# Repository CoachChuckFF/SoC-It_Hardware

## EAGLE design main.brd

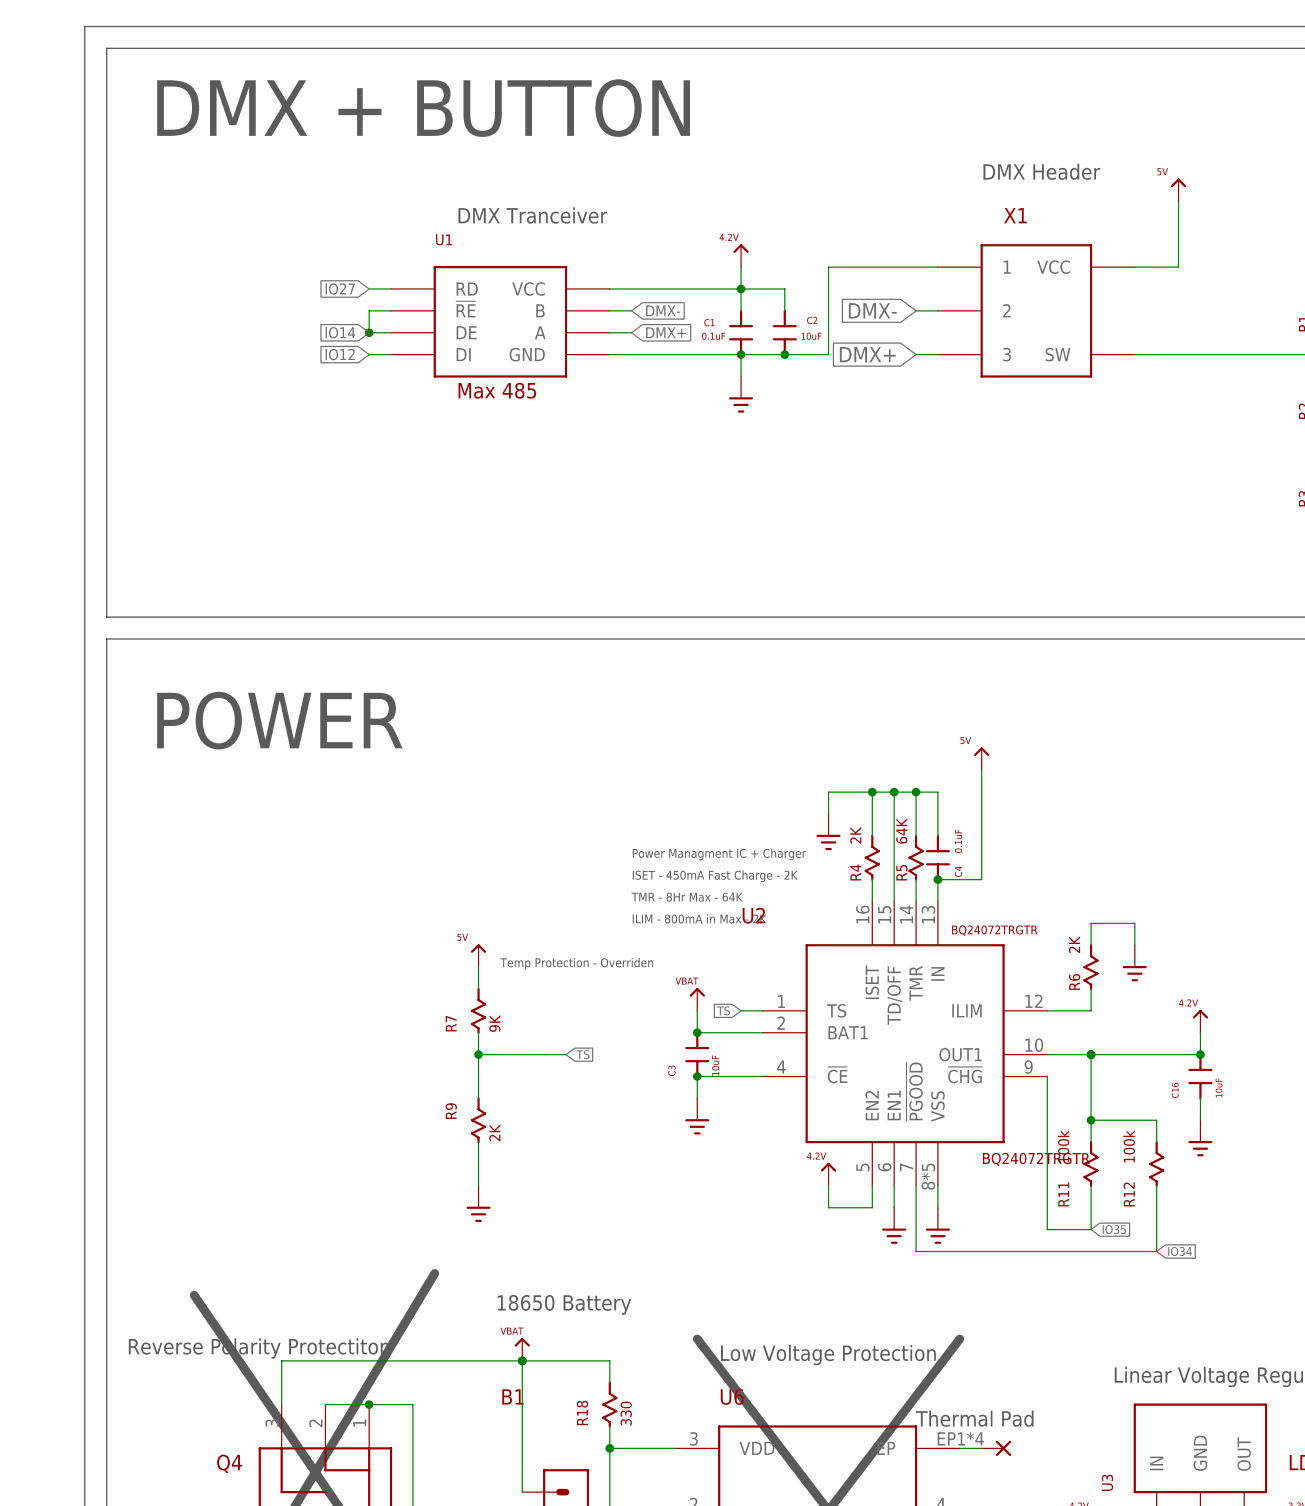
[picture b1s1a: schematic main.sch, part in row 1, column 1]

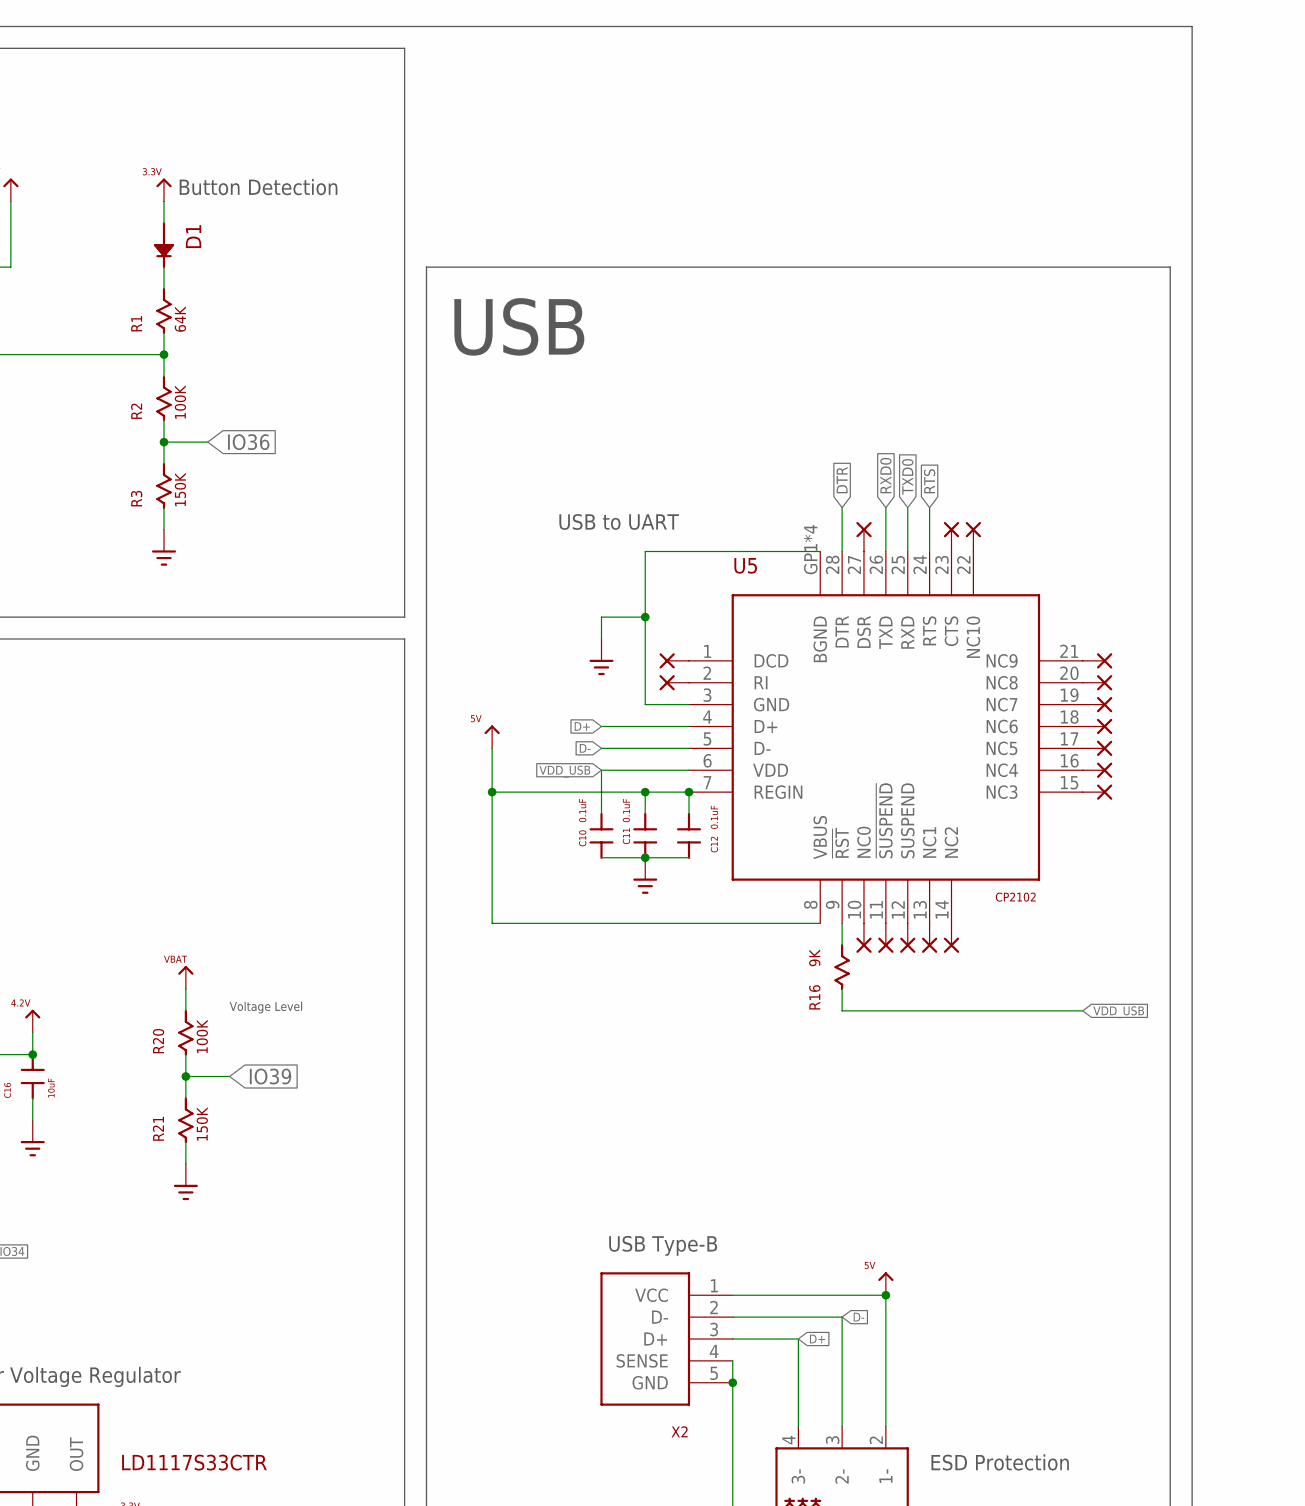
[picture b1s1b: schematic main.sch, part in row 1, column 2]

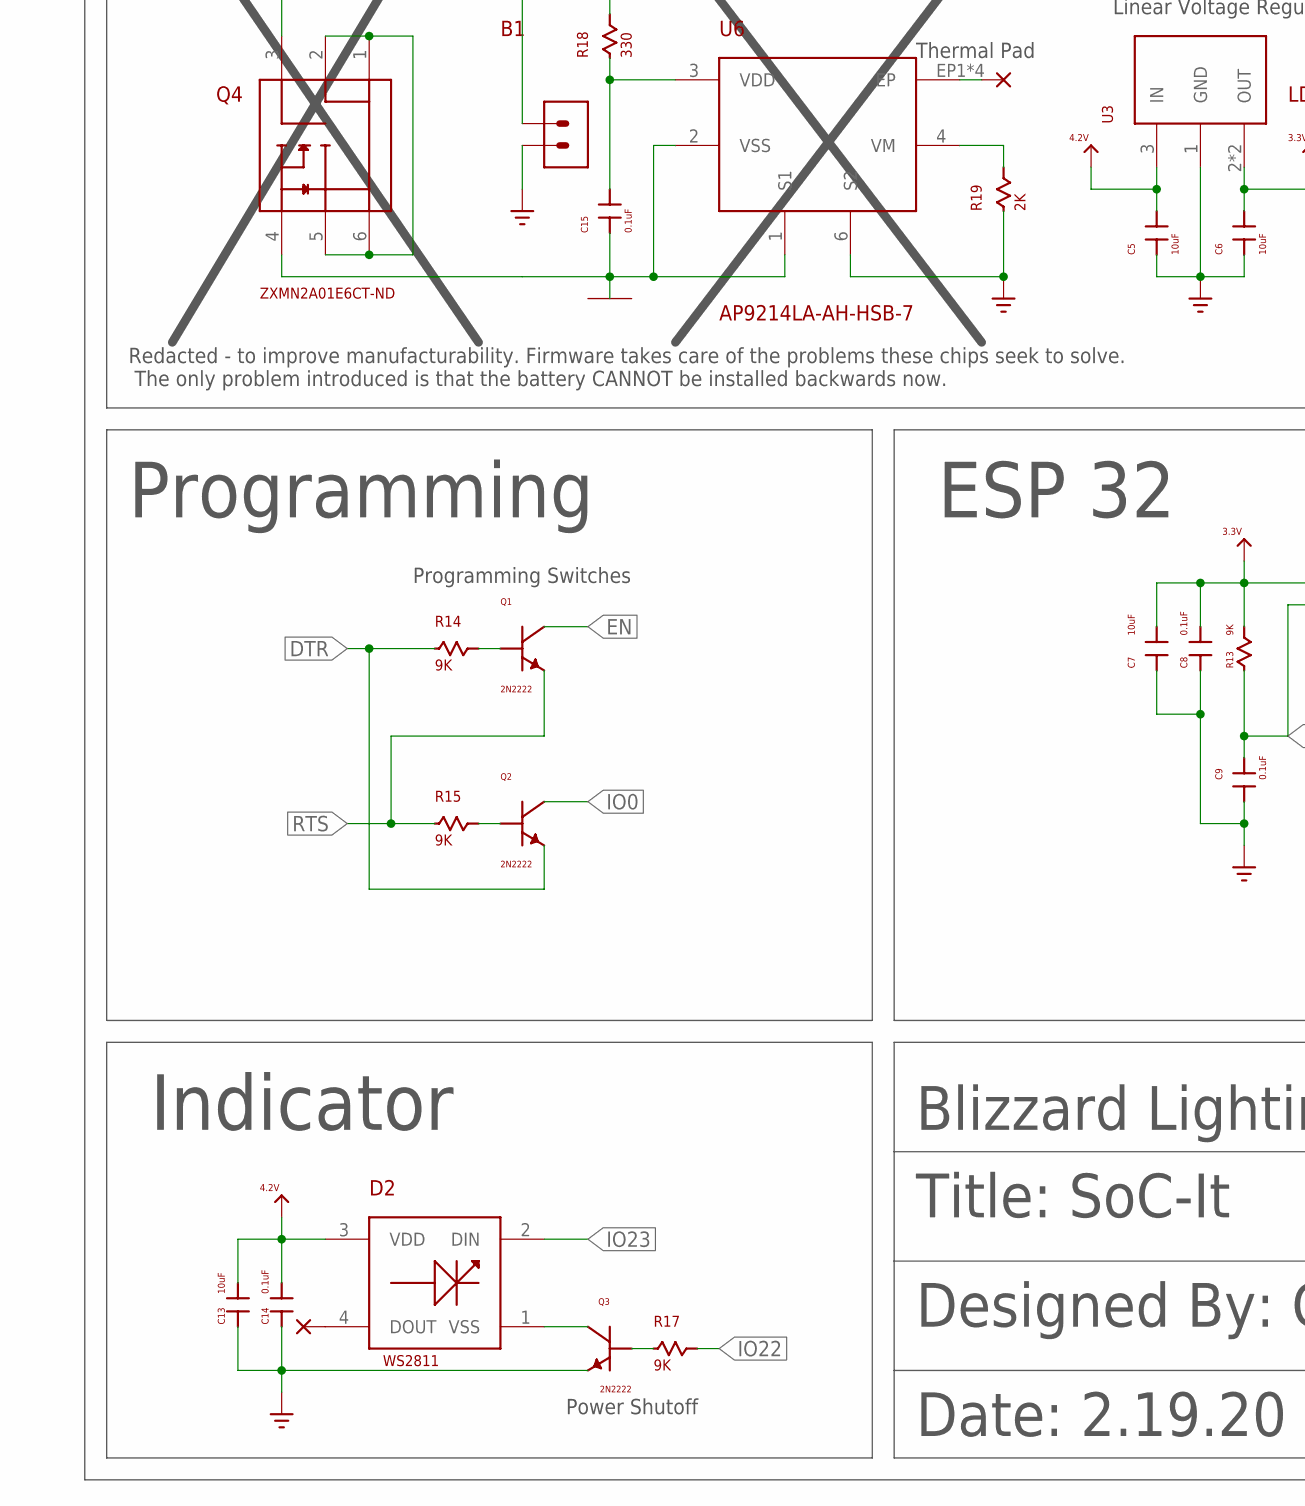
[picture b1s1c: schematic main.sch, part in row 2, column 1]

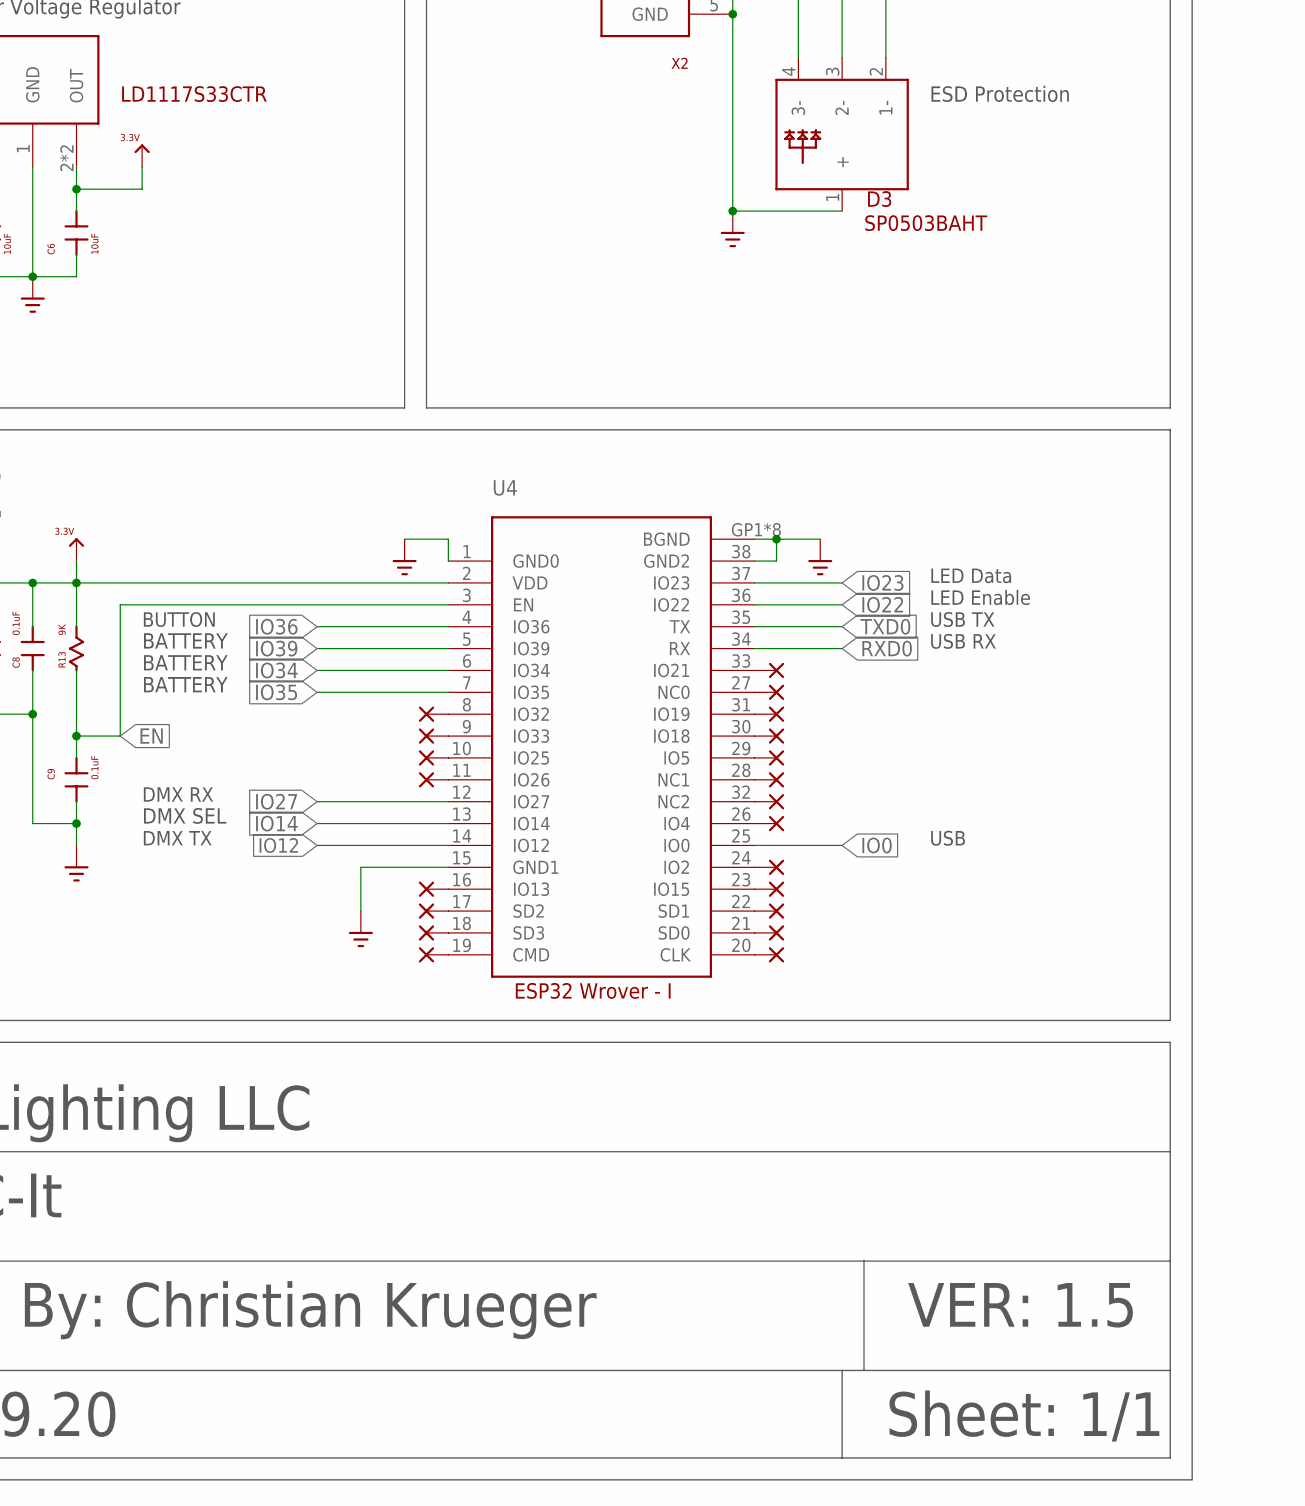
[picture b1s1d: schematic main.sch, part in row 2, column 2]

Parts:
B1: 18650_BATTERY_DEV; 18650_BATTERY_PKG
C1, C4, C8, C9, C10, C11, C12, C14, C15: 0.1uF; CAPC1508X55
C2, C3, C5, C6, C7, C13, C16: 10uF; CAPC1508X55
D1: 0603_DIODE_DEV; 0603_DIODE
D2: 5050_DEV; 5050_PKG
D3: USB_ESD_DEVSOT143; SOT192P237X122-4
Q1, Q2, Q3: 2N2222; SOT95P242X120-3
Q4: N_MOSFET_DEVSOT23-6L_PKG; SOT95P280X125-6
R1, R5: 64K; RESC1608X55
R2, R20: 100K; RESC1608X55
R3, R21: 150K; RESC1608X55
R4, R6, R9, R19: 2K; RESC1608X55
R7, R13, R14, R15, R16, R17: 9K; RESC1608X55
R11, R12: 100k; RESC1608X55
R18: 330; RESC1608X55
U1: MAX_485_DEV3D; SOIC127P600X175-8
U2: BQ24072TRGTR_DEVBQ24072TRGTR; QFN50P300X300X100-17T168
U3: LD1117S33CTR_DEVLD1117S33CTR; SOT230P700X180-4
U4: ESP_32_WROVER_I_PKG; ESP32_WROVER_I_PKG
U5: USB_TO_UART_DEV; QFN50P500X500X100-28
U6: AP9214L_DEV; U-DFN2535-6_PKG
X1: XLR_FEMALE_PLUG_DEV; XLR_FEMALE_PLUG_PKG
X2: USB_ALI_DEV; CHEAP_USB

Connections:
3.3V: C6.2, C7.2, C8.2, D1.A+, R13.2, U3.2 (OUT), U3.4 (OUT), U4.2 (VDD)
4.2V: C1.1, C2.1, C5.2, C13.2, C14.2, C16.2, D2.3 (VDD), R11.2, R12.2, U1.8 (VCC), U2.5 (EN2), U2.10 (OUT1), U3.3 (IN)
5V: C4.1, C11.2, C12.2, D3.2 (1-), R7.2, U2.13 (IN), U5.7 (REGIN), U5.8 (VBUS), X1.VCC, X2.1 (VCC)
BATTERY_GROUND: Q4.1 (D1), Q4.2 (D2), Q4.5 (D3), Q4.6 (D4)
D+: D3.4 (3-), U5.4 (D+), X2.3 (D+)
D-: D3.3 (2-), U5.5 (D-), X2.2 (D-)
DMX+: U1.6 (A), X1.3
DMX-: U1.7 (B), X1.2
DTR: Q2.2 (E), R14.1, U5.28 (DTR)
EN: C9.2, Q1.3 (C), R13.1, U4.3 (EN)
GND: B1.-, C1.2, C2.2, C3.1, C4.2, C5.1, C6.1, C7.1, C8.1, C9.1, C10.1, C11.1, C12.1, C13.1, C14.1, C16.1, D3.1 (+), Q3.2 (E), R3.1, R4.2, R5.2, R6.2, R9.1, R19.1, R21.1, U1.5 (GND), U2.4 (!CE), U2.6 (EN1), U2.8 (VSS), U2.15 (TD/OFF), U2.GP1 (VSS), U2.GP2 (VSS), U2.GP3 (VSS), U2.GP4 (VSS), U3.1 (GND), U4.1 (GND0), U4.15 (GND1), U4.38 (GND2), U4.GP1 (BGND), U4.GP2 (BGND), U4.GP3 (BGND), U4.GP4 (BGND), U4.GP5 (BGND), U4.GP6 (BGND), U4.GP8 (BGND), U4.GP9 (BGND), U5.3 (GND), U5.GP1 (BGND), U5.GP2 (BGND), U5.GP3 (BGND), U5.GP4 (BGND), U6.6 (S2), X1.1, X2.4 (SENSE), X2.5 (GND)
IO0: Q2.3 (C), U4.25 (IO0)
IO12: U1.4 (DI), U4.14 (IO12)
IO14: U1.2 (!RE), U1.3 (DE), U4.13 (IO14)
IO22: R17.2, U4.36 (IO22)
IO23: D2.2 (DIN), U4.37 (IO23)
IO27: U1.1 (RD), U4.12 (IO27)
IO34: R12.1, U2.7 (!PGOOD), U4.6 (IO34)
IO35: R11.1, U2.9 (!CHG), U4.7 (IO35)
IO36: R2.1, R3.2, U4.4 (IO36)
IO39: R20.1, R21.2, U4.5 (IO39)
unnamed: D2.1 (VSS), Q3.3 (C)
unnamed: Q1.1 (B), R14.2
unnamed: Q2.1 (B), R15.2
unnamed: Q3.1 (B), R17.1
unnamed: R16.2, U5.9 (!RST)
unnamed: D1.C-, R1.2
unnamed: R1.1, R2.2, X1.SW
unnamed: R19.2, U6.4 (VM)
unnamed: C15.2, R18.1, U6.3 (VDD)
unnamed: R6.1, U2.12 (ILIM)
unnamed: R5.1, U2.14 (TMR)
unnamed: R4.1, U2.16 (ISET)
PROTECTION_GROUND: C15.1, Q4.4 (S), U6.1 (S1), U6.2 (VSS)
PROTECTION_THERMAL_PAD: U6.EP1 (EP), U6.EP2 (EP), U6.EP3 (EP), U6.EP4 (EP)
RTS: Q1.2 (E), R15.1, U5.24 (RTS)
RXD0: U4.34 (RX), U5.26 (TXD)
TS: R7.1, R9.2, U2.1 (TS)
TXD0: U4.35 (TX), U5.25 (RXD)
VBAT: B1.+, C3.2, Q4.3 (G), R18.2, R20.2, U2.2 (BAT1)
VDD_USB: C10.2, R16.1, U5.6 (VDD)

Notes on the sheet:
USB
POWER
DMX RX
DMX TX
USB TX
USB RX
LED Data
DMX + BUTTON
ESP 32
Title: SoC-It
Designed By: Christian Krueger
Blizzard Lighting LLC
Date: 2.19.20
Sheet: 1/1
VER: 1.5
BUTTON
Programming Switches
USB Type-B
Linear Voltage Regulator
Max 485
DMX Header
DMX SEL
Programming
Indicator
BATTERY
LED Enable
CP2102
Button Detection
WS2811
ESD Protection
DMX Tranceiver
USB to UART
Power Shutoff
Thermal Pad
Low Voltage Protection
18650 Battery
BQ24072TRGTR
ISET - 450mA Fast Charge - 2K
TMR - 8Hr Max - 64K
ILIM - 800mA in Max - 2K

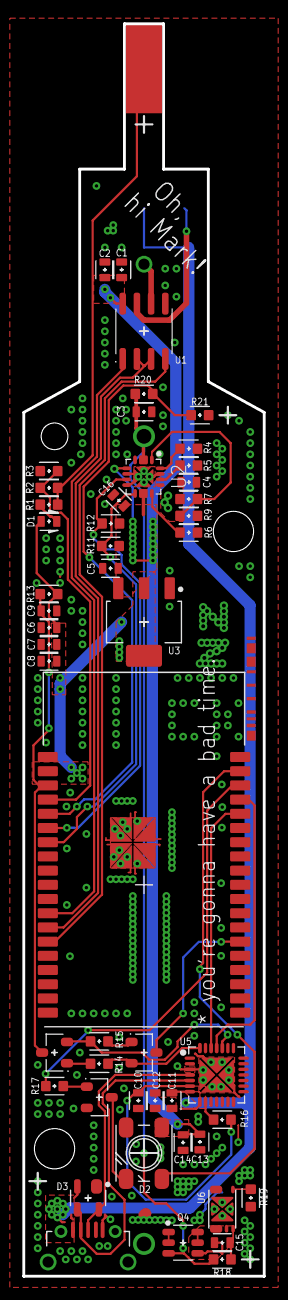
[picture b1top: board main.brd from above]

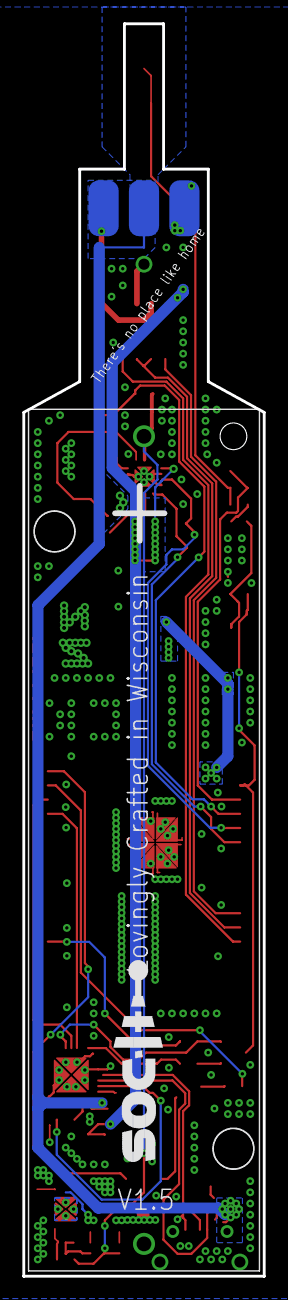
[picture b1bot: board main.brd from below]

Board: 2 copper layers, 21.5 x 112.0 mm, 51 parts (2 on the bottom side), 41 nets.

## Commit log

2019-06-18 added pnp ulp
2019-06-18 added pnp ulp fixed
2019-10-15 pnp file added
2019-10-15 pnp file updated
2019-12-18 V1_1
2020-02-19 fixed tab problems plus made some simplifications
2020-05-11 made the aperature size a bit bigger .3 -> .34
2020-05-12 v1.5
2020-07-16 made MNGT holes bigger
2020-07-17 redacted battery saftey chips
2020-07-23 SoC Out
2020-07-23 SoC signing off
